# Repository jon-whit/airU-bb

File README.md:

airU-bb
=====
The airU project is an interdisciplinary project by University of Utah Computer Science, Chemical Engineering, and Computer Engineering students who have designed a low cost air-quality sensor platform that is suited to improving our understanding of the Wasatch Front’s air quality challenges.  The project hopes to provide:

- A broad collection of air quality data, with tools that enable individuals to visualize, interpret, and download real-time data interactively.
- Low cost air quality stations that can communicate wireless with centralized databases (be it government or commercial)
- Innovative transportation routes based on air quality index rating (long term)

Contribute
----------
Please see the contribution guidelines in [CONTRIBUTING.md](./CONTRIBUTING.md).

- Issue Tracker: https://github.com/jon-whit/airU-bb/issues
- Source Code: https://github.com/jon-whit/airU-bb

Support
-------
If you are having issues, please feel free to email us.

We have a mailing list located at: airu-help@utah.edu

License
-------
See [LICENSE.md](./LICENSE.md)

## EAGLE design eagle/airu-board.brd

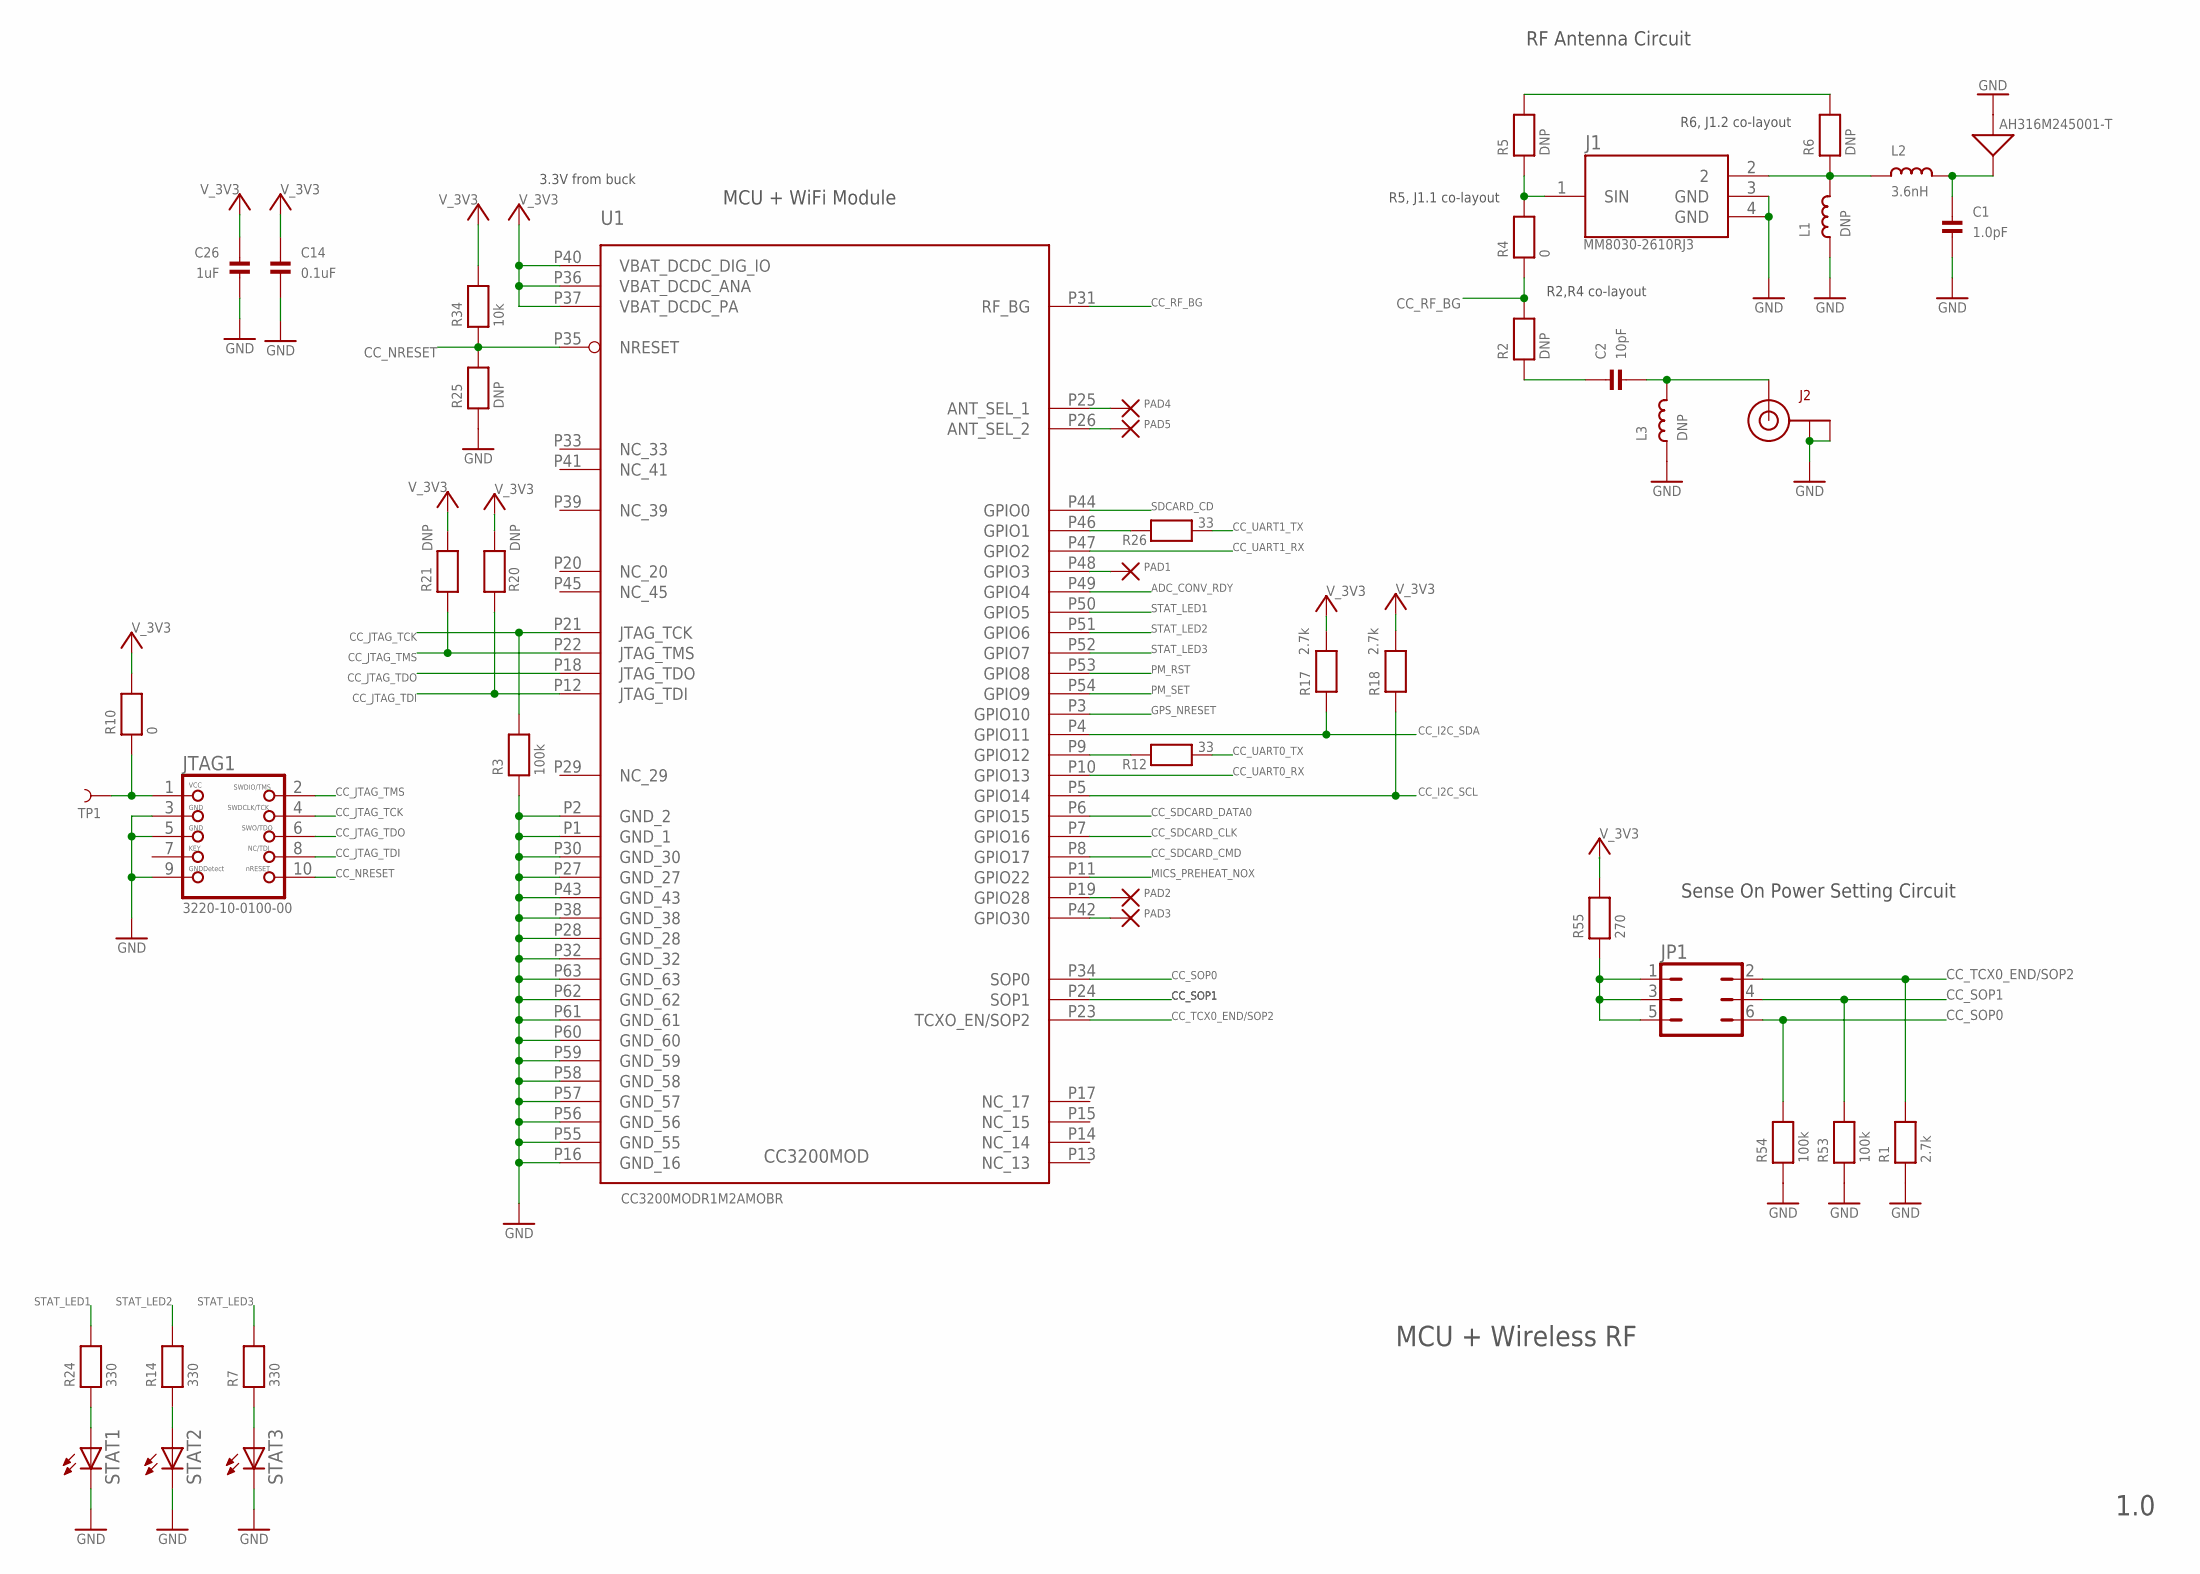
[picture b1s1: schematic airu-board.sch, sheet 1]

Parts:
C1: 1.0pF; 0402
C2: 10pF; 0402
C14: 0.1uF; 0402
C26: 1uF; 0402
E1: AH316M245001-T; AH316M
J1: MM8030-2610RJ3; MURATA_MM8030-2610RJ3
J2: U.FL-R-SMT-1(10); U.FL
JP1: JP3Q
JTAG1: 3220-10-0100-00; CORTEXM3_SWD10_MOLEX; MANUFACTURER_PART_NUMBER 3220-10-0100-00
L1, L3: DNP; _0402
L2: 3.6nH; _0402
PAD1, PAD2, PAD3, PAD4, PAD5: 2,54/1,0
R1, R17, R18: 2.7k; 0402
R2, R5, R6, R20, R21, R25: DNP; 0402
R3, R53, R54: 100k; 0402
R4, R10: 0; 0402
R7, R14, R24: 330; 0402
R12, R26: 33; 0402
R34: 10k; 0402
R55: 270; 0402
STAT1, STAT2, STAT3: LEDCHIPLED_0603; CHIPLED_0603
TP1: TEST-POINT2; PAD.02X.02
U1: CC3200MODR1M2AMOBR; CC3200MOD

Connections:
ADC_CONV_RDY: U1.P49 (GPIO4); also elsewhere on the board
CC_I2C_SCL: R18.1, U1.P5 (GPIO14); also elsewhere on the board
CC_I2C_SDA: R17.1, U1.P4 (GPIO11); also elsewhere on the board
CC_JTAG_TCK: JTAG1.4, R3.2, U1.P21 (JTAG_TCK)
CC_JTAG_TDI: JTAG1.8, R20.1, U1.P12 (JTAG_TDI)
CC_JTAG_TDO: JTAG1.6, U1.P18 (JTAG_TDO)
CC_JTAG_TMS: JTAG1.2, R21.1, U1.P22 (JTAG_TMS)
CC_NRESET: JTAG1.10, R25.2, R34.1, U1.P35 (NRESET); also elsewhere on the board
CC_RF_BG: R2.2, R4.1, U1.P31 (RF_BG)
CC_SDCARD_CLK: U1.P7 (GPIO16); also elsewhere on the board
CC_SDCARD_CMD: U1.P8 (GPIO17); also elsewhere on the board
CC_SDCARD_DATA0: U1.P6 (GPIO15); also elsewhere on the board
CC_SOP0: JP1.6, R54.2, U1.P34 (SOP0)
CC_SOP1: JP1.4, R53.2, U1.P24 (SOP1)
CC_TCX0_END/SOP2: JP1.2, R1.2, U1.P23 (TCXO_EN/SOP2)
CC_UART0_RX: U1.P10 (GPIO13); also elsewhere on the board
CC_UART0_TX: R12.2; also elsewhere on the board
CC_UART1_RX: U1.P47 (GPIO2); also elsewhere on the board
CC_UART1_TX: R26.2; also elsewhere on the board
GND: C1.2, C14.2, C26.2, E1.P$2, J1.3 (GND), J1.4 (GND), J2.1 (GND), J2.2 (GND), JTAG1.3, JTAG1.5, JTAG1.9, L1.1, L3.1, R1.1, R3.1, R25.1, R53.1, R54.1, STAT1.C, STAT2.C, STAT3.C, U1.P1 (GND_1), U1.P2 (GND_2), U1.P16 (GND_16), U1.P27 (GND_27), U1.P28 (GND_28), U1.P30 (GND_30), U1.P32 (GND_32), U1.P38 (GND_38), U1.P43 (GND_43), U1.P55 (GND_55), U1.P56 (GND_56), U1.P57 (GND_57), U1.P58 (GND_58), U1.P59 (GND_59), U1.P60 (GND_60), U1.P61 (GND_61), U1.P62 (GND_62), U1.P63 (GND_63); also elsewhere on the board
GPS_NRESET: U1.P3 (GPIO10); also elsewhere on the board
MICS_PREHEAT_NOX: U1.P11 (GPIO22); also elsewhere on the board
unnamed: J1.1 (SIN), R4.2, R5.1
unnamed: R5.2, R6.2
unnamed: J1.2, L1.2, L2.1, R6.1
unnamed: C1.1, E1.P$1, L2.2
unnamed: C2.1, R2.1
unnamed: C2.2, J2.3 (SIGNAL), L3.2
unnamed: JTAG1.1, R10.1, TP1.P$1
unnamed: R12.1, U1.P9 (GPIO12)
unnamed: R26.1, U1.P46 (GPIO1)
unnamed: R24.1, STAT1.A
unnamed: R14.1, STAT2.A
unnamed: R7.1, STAT3.A
unnamed: PAD1.1, U1.P48 (GPIO3)
unnamed: PAD2.1, U1.P19 (GPIO28)
unnamed: PAD3.1, U1.P42 (GPIO30)
unnamed: PAD4.1, U1.P25 (ANT_SEL_1)
unnamed: PAD5.1, U1.P26 (ANT_SEL_2)
unnamed: JP1.1, JP1.3, JP1.5, R55.1
PM_RST: U1.P53 (GPIO8); also elsewhere on the board
PM_SET: U1.P54 (GPIO9); also elsewhere on the board
SDCARD_CD: U1.P44 (GPIO0); also elsewhere on the board
STAT_LED1: R24.2, U1.P50 (GPIO5)
STAT_LED2: R14.2, U1.P51 (GPIO6)
STAT_LED3: R7.2, U1.P52 (GPIO7)
V_3V3: C14.1, C26.1, R10.2, R17.2, R18.2, R20.2, R21.2, R34.2, R55.2, U1.P36 (VBAT_DCDC_ANA), U1.P37 (VBAT_DCDC_PA), U1.P40 (VBAT_DCDC_DIG_IO); also elsewhere on the board

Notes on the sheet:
R2,R4 co-layout
R5, J1.1 co-layout
R6, J1.2 co-layout
3.3V from buck
1.0
MCU + Wireless RF
RF Antenna Circuit
Sense On Power Setting Circuit
MCU + WiFi Module

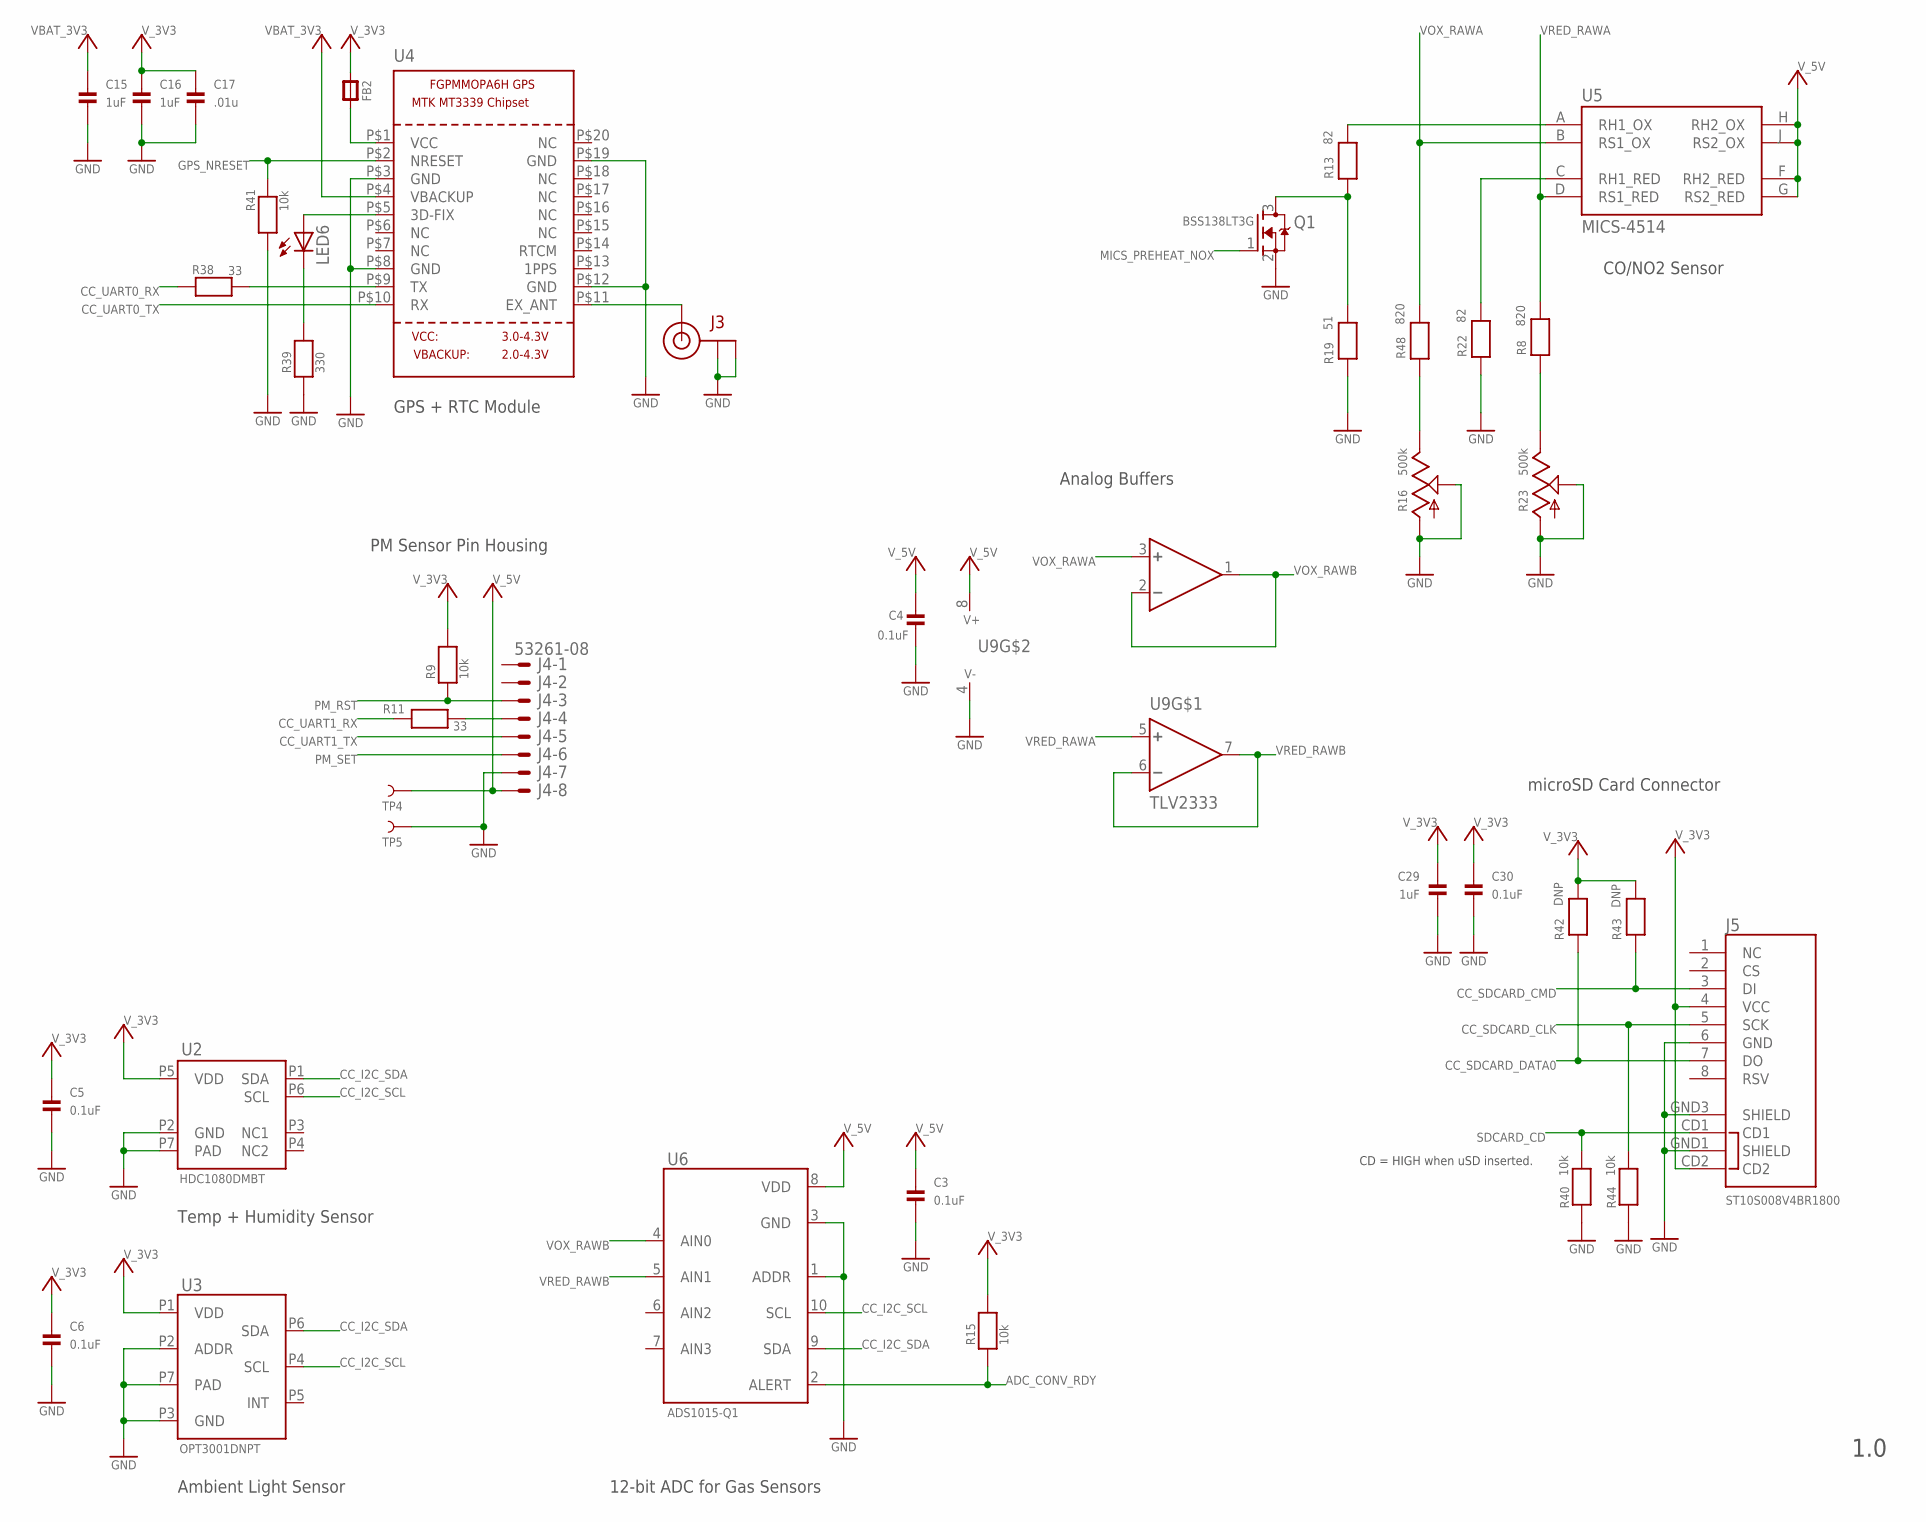
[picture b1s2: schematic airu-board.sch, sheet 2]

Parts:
C3, C4, C5, C6, C30: 0.1uF; _0402
C15, C16, C29: 1uF; _0402
C17: .01u; _0402
FB2: FERRITE_0402; _0402
J3: U.FL-R-SMT-1(10); U.FL
J4: 53261-08
J5: ST10S008V4BR1800; MICROSD_1:1; MANUFACTURER_PART_NUMBER ST10S008V4BR1800
LED6: LEDCHIPLED_0603; CHIPLED_0603
Q1: BSS138LT3G; SOT23
R8, R48: 820; 0402
R9, R15, R40, R41, R44: 10k; 0402
R11, R38: 33; 0402
R13, R22: 82; 0402
R16, R23: 500k; B25P
R19: 51; 0402
R39: 330; 0402
R42, R43: DNP; 0402
TP4, TP5: TEST-POINT2; PAD.02X.02
U2: HDC1080DMBT; WSON
U3: OPT3001DNPT; USON
U4: GPS_FGPMMOPA6H; FGPMMOPA6H
U5: MICS-4514; MICS_10-SMD
U6: ADS1015-Q1; S-PDSO-G10
U9: TLV2333; DGK_S-PDSO-G8

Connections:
ADC_CONV_RDY: R15.1, U6.2 (ALERT); also elsewhere on the board
CC_I2C_SCL: U2.P6 (SCL), U3.P4 (SCL), U6.10 (SCL); also elsewhere on the board
CC_I2C_SDA: U2.P1 (SDA), U3.P6 (SDA), U6.9 (SDA); also elsewhere on the board
CC_SDCARD_CLK: J5.5 (SCK), R44.2; also elsewhere on the board
CC_SDCARD_CMD: J5.3 (DI), R43.1; also elsewhere on the board
CC_SDCARD_DATA0: J5.7 (DO), R42.1; also elsewhere on the board
CC_UART0_RX: R38.1; also elsewhere on the board
CC_UART0_TX: U4.P$10 (RX); also elsewhere on the board
CC_UART1_RX: R11.1; also elsewhere on the board
CC_UART1_TX: J4.5; also elsewhere on the board
GND: C3.2, C4.2, C5.2, C6.2, C15.2, C16.2, C17.2, C29.2, C30.2, J3.1 (GND), J3.2 (GND), J4.7, J5.6 (GND), J5.GND1 (SHIELD), J5.GND3 (SHIELD), Q1.2 (S), R16.A, R16.S, R19.1, R22.1, R23.A, R23.S, R39.1, R40.1, R41.1, R44.1, TP5.P$1, U2.P2 (GND), U2.P7 (PAD), U3.P2 (ADDR), U3.P3 (GND), U3.P7 (PAD), U4.P$3 (GND), U4.P$8 (GND), U4.P$12 (GND), U4.P$19 (GND), U6.1 (ADDR), U6.3 (GND), U9.4 (V-); also elsewhere on the board
GPS_NRESET: R41.2, U4.P$2 (NRESET); also elsewhere on the board
MICS_PREHEAT_NOX: Q1.1 (G); also elsewhere on the board
unnamed: J4.4, R11.2
unnamed: R13.2, U5.A (RH1_OX)
unnamed: Q1.3 (D), R13.1, R19.2
unnamed: R22.2, U5.C (RH1_RED)
unnamed: R16.E, R48.1
unnamed: R8.1, R23.E
unnamed: J3.3 (SIGNAL), U4.P$11 (EX_ANT)
unnamed: LED6.A, U4.P$5 (3D-FIX)
unnamed: LED6.C, R39.2
unnamed: R38.2, U4.P$9 (TX)
PM_RST: J4.3, R9.1; also elsewhere on the board
PM_SET: J4.6; also elsewhere on the board
SDCARD_CD: J5.CD1, R40.2; also elsewhere on the board
VBAT_3V3: C15.1, U4.P$4 (VBACKUP); also elsewhere on the board
VOX_RAWA: R48.2, U5.B (RS1_OX), U9.3 (+)
VOX_RAWB: U6.4 (AIN0), U9.1 (OUT), U9.2 (-)
VRED_RAWA: R8.2, U5.D (RS1_RED), U9.5 (+1)
VRED_RAWB: U6.5 (AIN1), U9.6 (-1), U9.7 (OUT1)
V_3V3: C5.1, C6.1, C16.1, C17.1, C29.1, C30.1, FB2.1, FB2.2, J5.4 (VCC), J5.CD2, R9.2, R15.2, R42.2, R43.2, U2.P5 (VDD), U3.P1 (VDD), U4.P$1 (VCC); also elsewhere on the board
V_5V: C3.1, C4.1, J4.8, TP4.P$1, U5.F (RH2_RED), U5.G (RS2_RED), U5.H (RH2_OX), U5.J (RS2_OX), U6.8 (VDD), U9.8 (V+); also elsewhere on the board

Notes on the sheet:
CD = HIGH when uSD inserted.
1.0
GPS + RTC Module
Temp + Humidity Sensor
Ambient Light Sensor
PM Sensor Pin Housing
microSD Card Connector
CO/NO2 Sensor
12-bit ADC for Gas Sensors
Analog Buffers

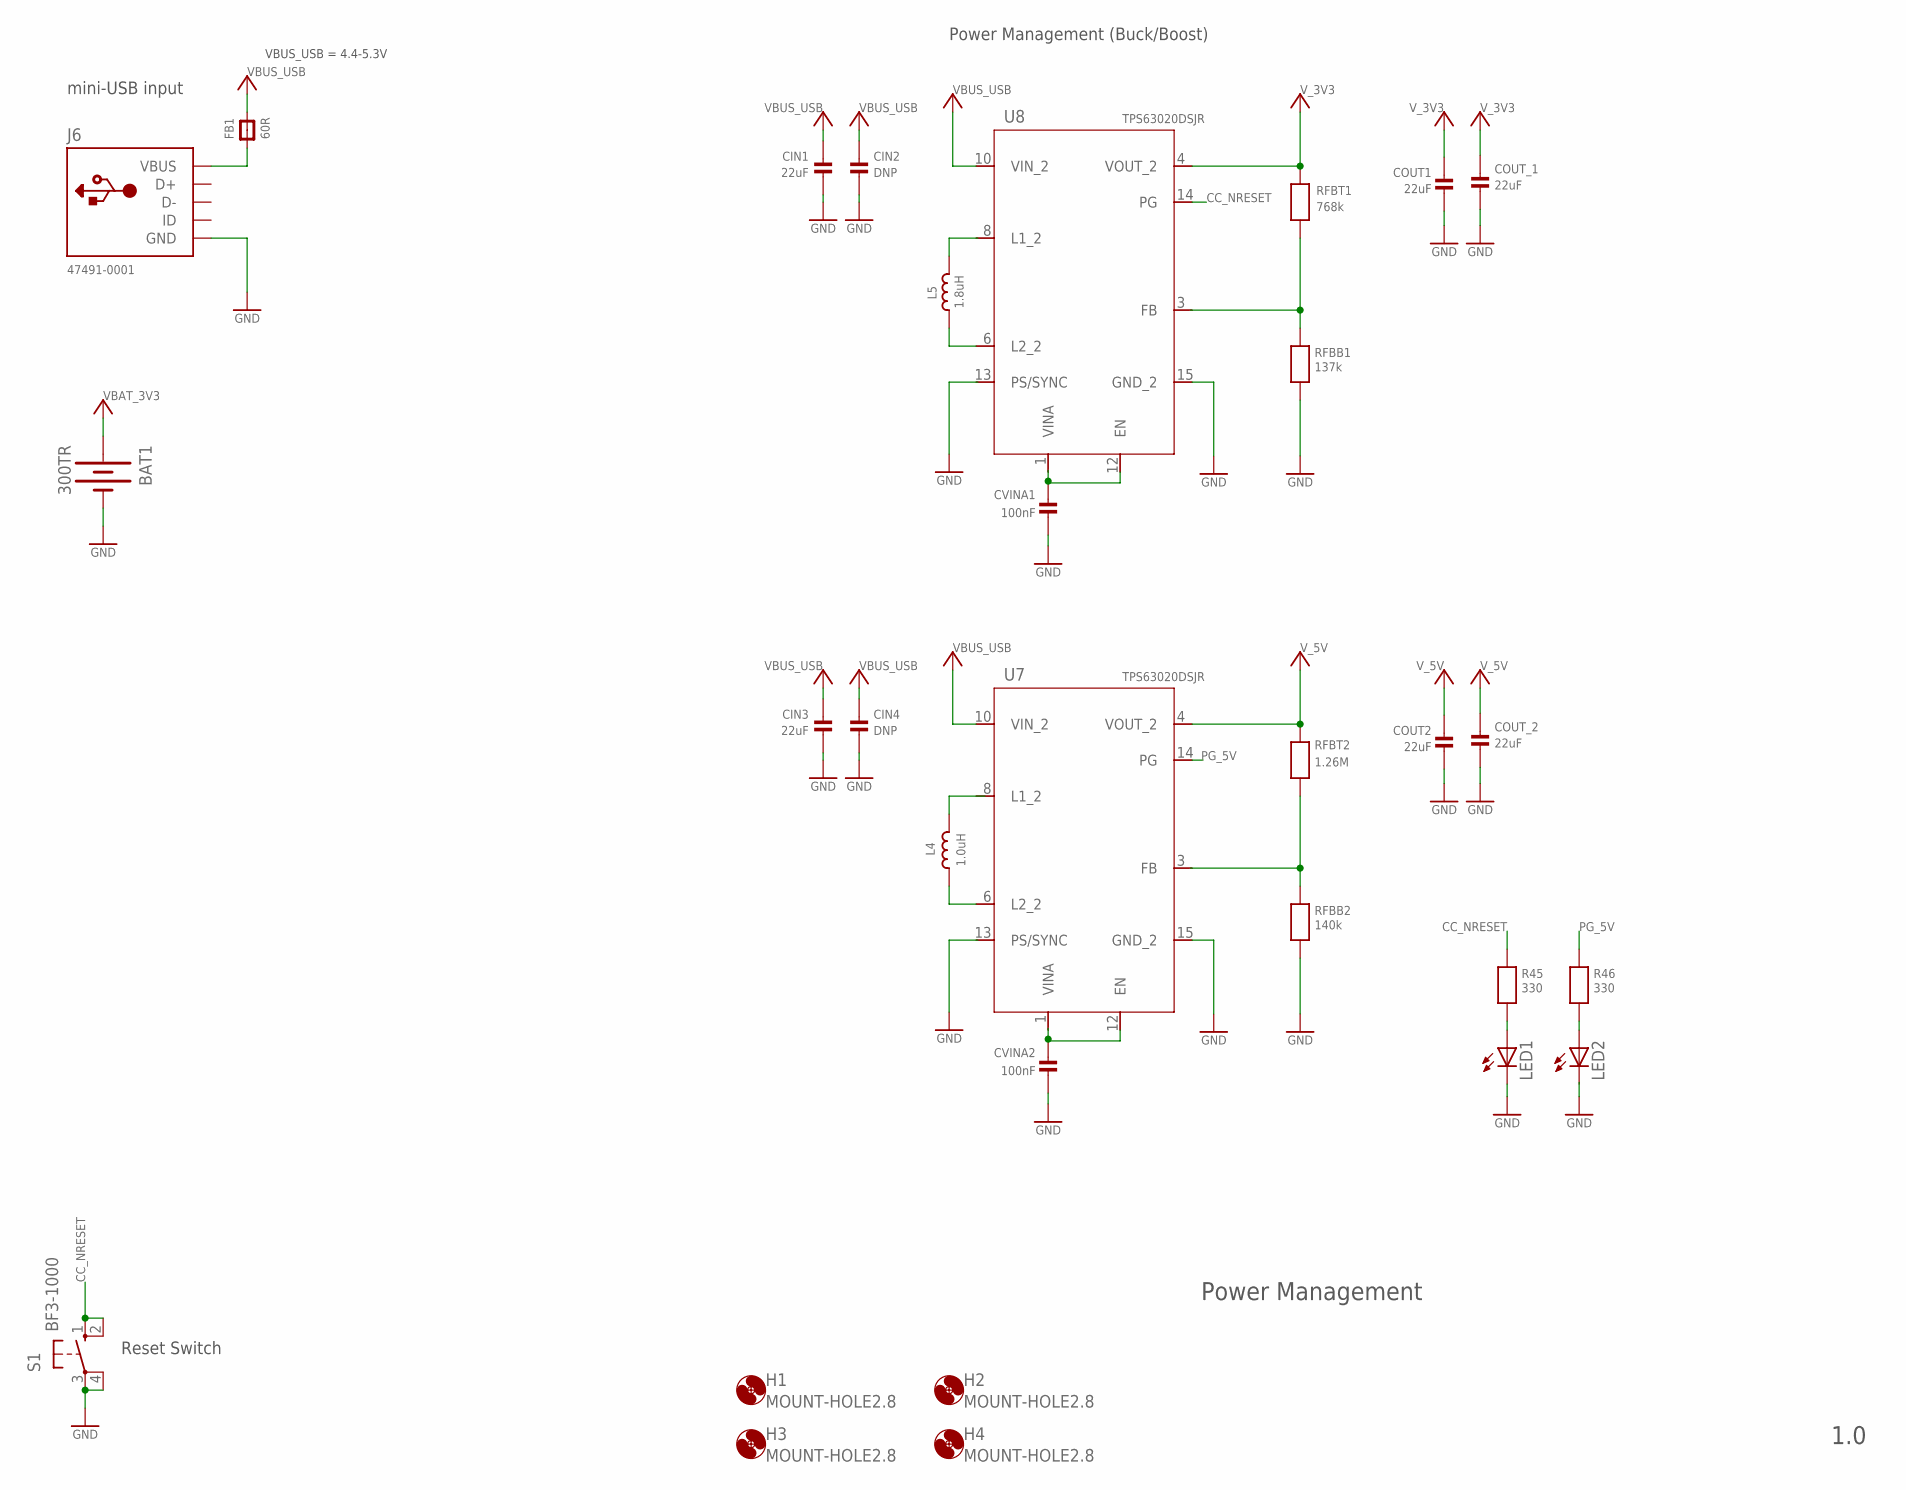
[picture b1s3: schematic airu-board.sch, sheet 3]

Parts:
BAT1: 300TR; BATTCON_12MM; MANUFACTURER_PART_NUMBER 300TR
CIN1, CIN3: 22uF; 1206_190
CIN2, CIN4: DNP; 1206_190
COUT1, COUT2: 22uF; 0805
COUT_1, COUT_2: 22uF; 0805
CVINA1, CVINA2: 100nF; 0603
FB1: 60R; _0402
H1, H2, H3, H4: MOUNT-HOLE2.8; 2,8
J6: 47491-0001; USB-MINIB; MANUFACTURER_PART_NUMBER 47491-0001
L4: 1.0uH; SRN3015
L5: 1.8uH; SDR0403
LED1, LED2: LEDCHIPLED_0603; CHIPLED_0603
R45, R46: 330; 0402
RFBB1: 137k; 0402
RFBB2: 140k; 0402
RFBT1: 768k; 0402
RFBT2: 1.26M; 0805
S1: BF3-1000; B3F-10XX
U7, U8: TPS63020DSJR; R-PVSON-N14

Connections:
CC_NRESET: R45.P1 (1), S1.1 (S), S1.2 (S1), U8.14 (PG); also elsewhere on the board
GND: BAT1.GND (-), CIN1.2, CIN2.2, CIN3.2, CIN4.2, COUT1.2, COUT2.2, COUT_1.2, COUT_2.2, CVINA1.2, CVINA2.2, J6.GND, LED1.C, RFBB1.P2 (2), RFBB2.P2 (2), S1.3, S1.4 (P1), U7.15 (GND_2), U8.15 (GND_2); also elsewhere on the board
unnamed: CVINA1.1, U8.12 (EN)
unnamed: L5.1, U8.6 (L2_2)
unnamed: L4.1, U7.6 (L2_2)
unnamed: RFBB1.P1 (1), RFBT1.P2 (2)
unnamed: RFBB2.P1 (1), RFBT2.2
unnamed: CVINA2.1, U7.12 (EN)
unnamed: LED2.A, R46.P2 (2)
unnamed: LED1.A, R45.P2 (2)
unnamed: FB1.1, J6.VBUS
PG_5V: R46.P1 (1), U7.14 (PG)
VBAT_3V3: BAT1.PWR@1 (+); also elsewhere on the board
VBUS_USB: CIN1.1, CIN2.1, CIN3.1, CIN4.1, FB1.2, U7.10 (VIN_2), U8.10 (VIN_2)
V_3V3: COUT1.1, COUT_1.1, RFBT1.P1 (1), U8.4 (VOUT_2); also elsewhere on the board
V_5V: COUT2.1, COUT_2.1, RFBT2.1, U7.4 (VOUT_2); also elsewhere on the board

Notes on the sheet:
Reset Switch
VBUS_USB = 4.4-5.3V
Power Management
1.0
Power Management (Buck/Boost)
mini-USB input

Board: 2 copper layers, 113 parts (12 on the bottom side), 74 nets, no tracks yet.

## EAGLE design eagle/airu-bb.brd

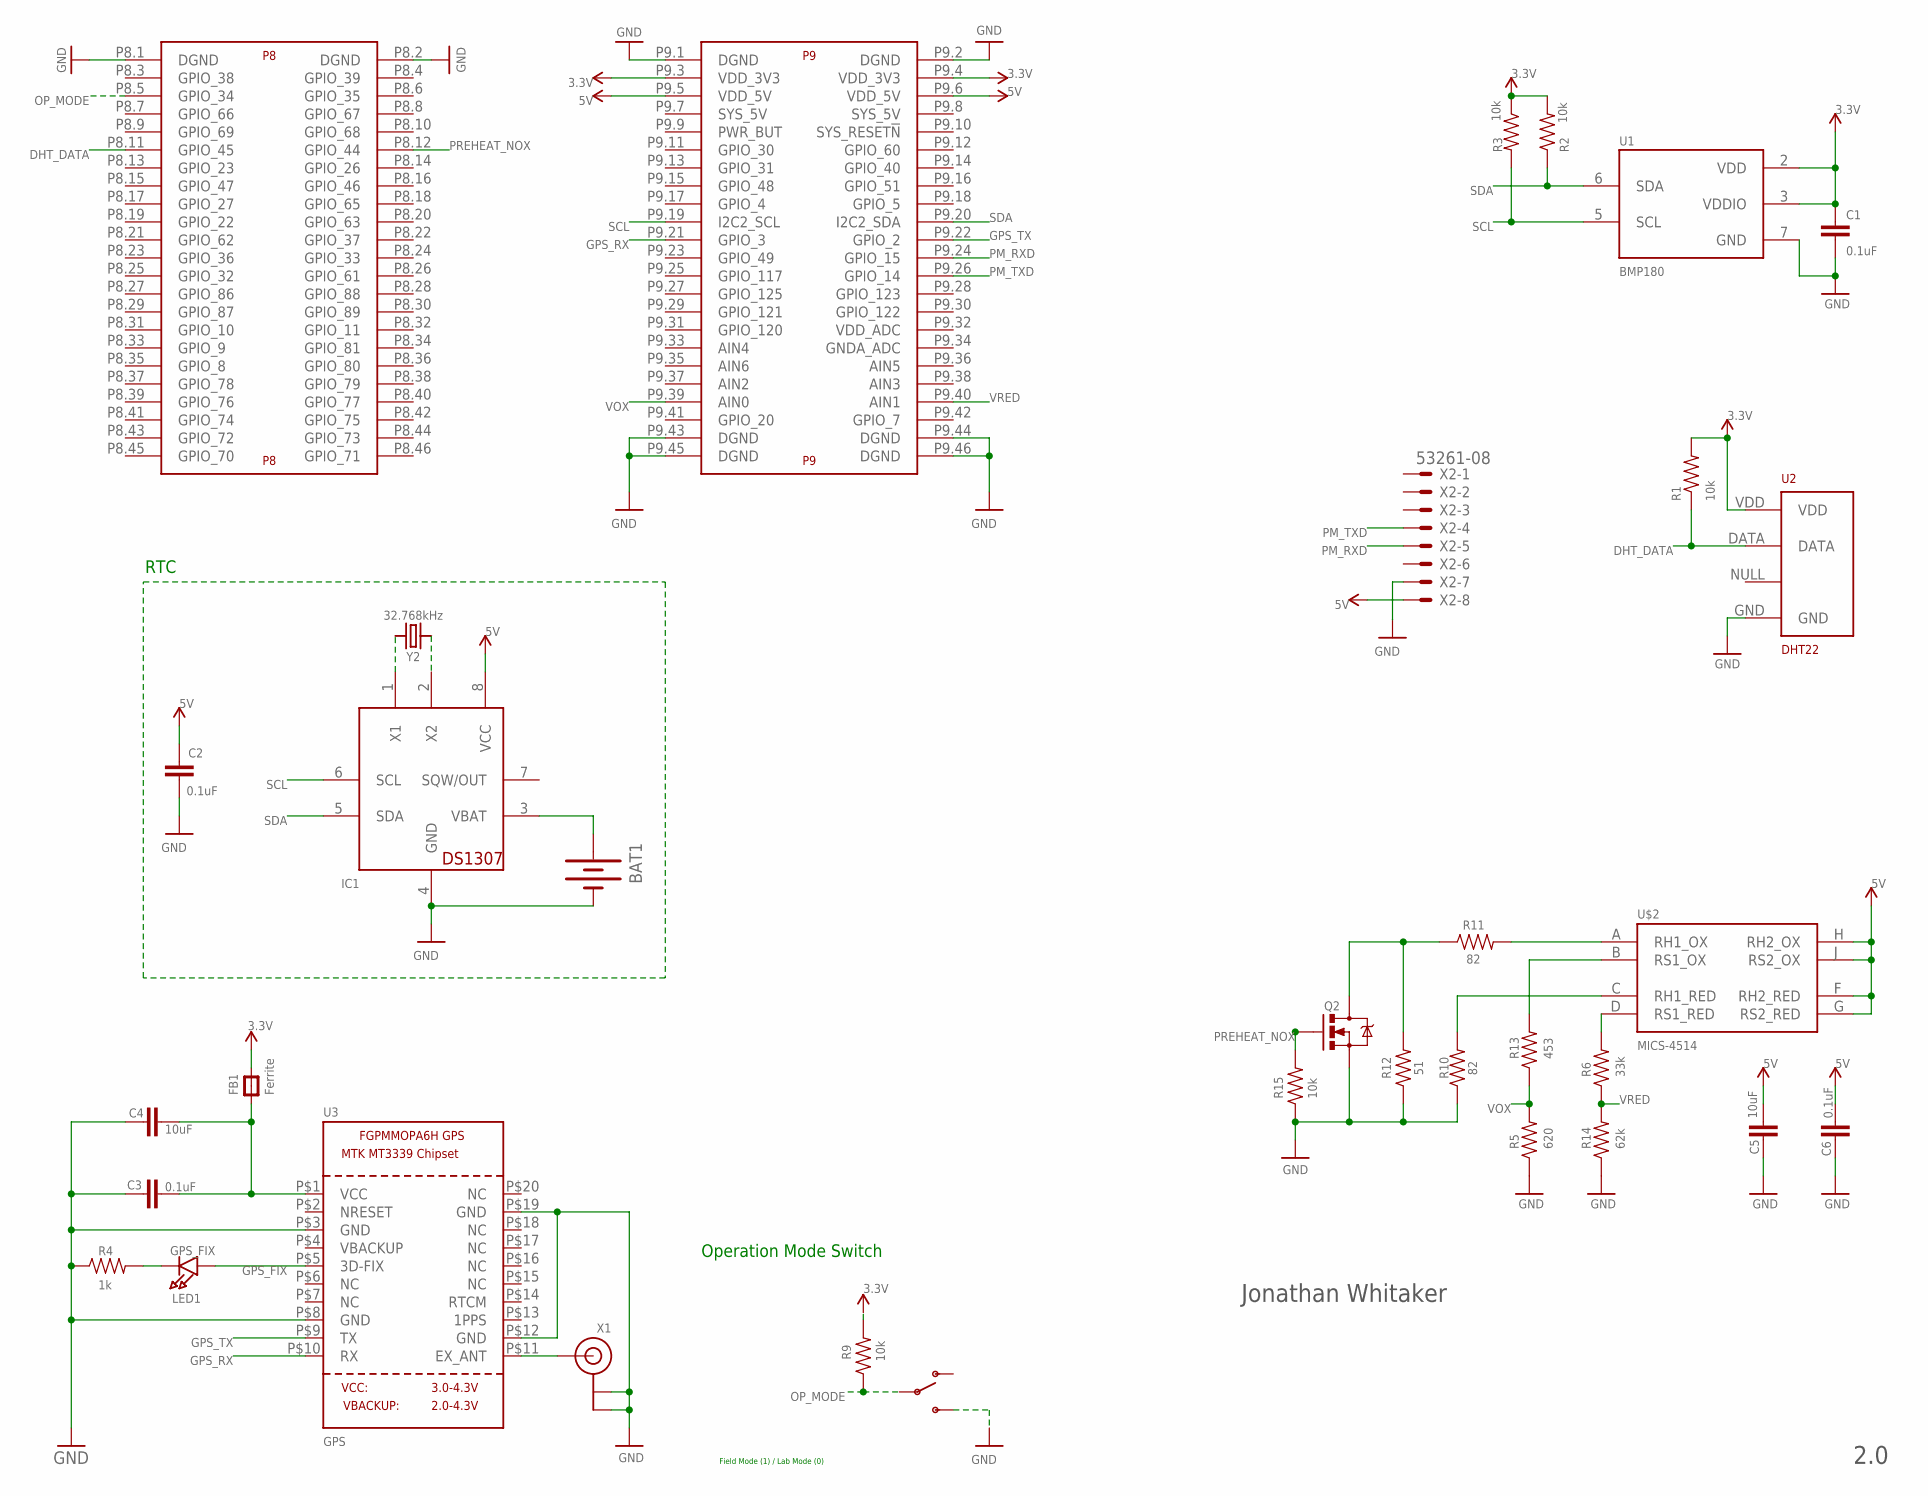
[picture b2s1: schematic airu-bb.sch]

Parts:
BAT1: BATTERY20SMD; BATTCON_20MM
C1, C2, C3, C6: 0.1uF; 1206
C4, C5: 10uF; 1206
FB1: Ferrite; 0805
IC1: DS1307; DIL08
LED1: GPS_FIX; CHIPLED_1206
Q2: MOSFET-NCHANNELAO3404A; SOT23-3
R1, R2, R3, R9, R15: 10k; 1206
R4: 1k; 1206
R5: 620; 1206
R6: 33k; 1206
R10, R11: 82; 1206
R12: 51; 1206
R13: 453; 1206
R14: 62k; 1206
U1: BMP180
U2: DHT22; RHT03_DHT-22
U3: GPS; FGPMMOPA6H
U$1: BEAGLE_BONE_BLACK_CAPE
U$2: MICS-4514; MICS_10-SMD
U$3: SWITCH_SPDT; KPS-1290
X1: ANTENNA_U.FL; U.FL
X2: 53261-08
Y2: 32.768kHz; 2-SMD

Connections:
3.3V: C1.1, FB1.2, R1.2, R2.2, R3.1, R9.2, U1.2 (VDD), U1.3 (VDDIO), U2.VDD, U$1.P9.3 (VDD_3V3), U$1.P9.4 (VDD_3V3)
5V: C2.2, C5.2, C6.2, IC1.8 (VCC), U$1.P9.5 (VDD_5V), U$1.P9.6 (VDD_5V), U$2.F (RH2_RED), U$2.G (RS2_RED), U$2.H (RH2_OX), U$2.J (RS2_OX), X2.8
DHT_DATA: R1.1, U2.DATA, U$1.P8.11 (GPIO_45)
GND: BAT1.2 (-), C1.2, C2.1, C3.1, C4.1, C5.1, C6.1, IC1.4 (GND), Q2.2 (S), R4.1, R5.1, R10.1, R12.1, R14.1, R15.1, U1.7 (GND), U2.GND, U3.P$3 (GND), U3.P$8 (GND), U3.P$12 (GND), U3.P$19 (GND), U$1.P8.1 (DGND), U$1.P8.2 (DGND), U$1.P9.1 (DGND), U$1.P9.2 (DGND), U$1.P9.43 (DGND), U$1.P9.44 (DGND), U$1.P9.45 (DGND), U$1.P9.46 (DGND), U$3.S, X1.1 (GND), X1.2 (GND), X2.7
GPS_FIX: LED1.A, U3.P$5 (3D-FIX)
GPS_RX: U3.P$10 (RX), U$1.P9.21 (GPIO_3)
GPS_TX: U3.P$9 (TX), U$1.P9.22 (GPIO_2)
unnamed: C3.2, C4.2, FB1.1, U3.P$1 (VCC)
unnamed: U3.P$11 (EX_ANT), X1.3 (SIGNAL)
unnamed: LED1.C, R4.2
unnamed: R10.2, U$2.C (RH1_RED)
unnamed: R13.2, U$2.B (RS1_OX)
unnamed: Q2.3 (D), R11.1, R12.2
unnamed: R6.2, U$2.D (RS1_RED)
unnamed: R11.2, U$2.A (RH1_OX)
unnamed: BAT1.1 (+), IC1.3 (VBAT)
unnamed: IC1.1 (X1), Y2.1
unnamed: IC1.2 (X2), Y2.2
OP_MODE: R9.1, U$1.P8.5 (GPIO_34), U$3.P
PM_RXD: U$1.P9.24 (GPIO_15), X2.5
PM_TXD: U$1.P9.26 (GPIO_14), X2.4
PREHEAT_NOX: Q2.1 (G), R15.2, U$1.P8.12 (GPIO_44)
SCL: IC1.6 (SCL), R3.2, U1.5 (SCL), U$1.P9.19 (I2C2_SCL)
SDA: IC1.5 (SDA), R2.1, U1.6 (SDA), U$1.P9.20 (I2C2_SDA)
VOX: R5.2, R13.1, U$1.P9.39 (AIN0)
VRED: R6.1, R14.2, U$1.P9.40 (AIN1)

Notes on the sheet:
Jonathan Whitaker
2.0
RTC
Operation Mode Switch
Field Mode (1) / Lab Mode (0)

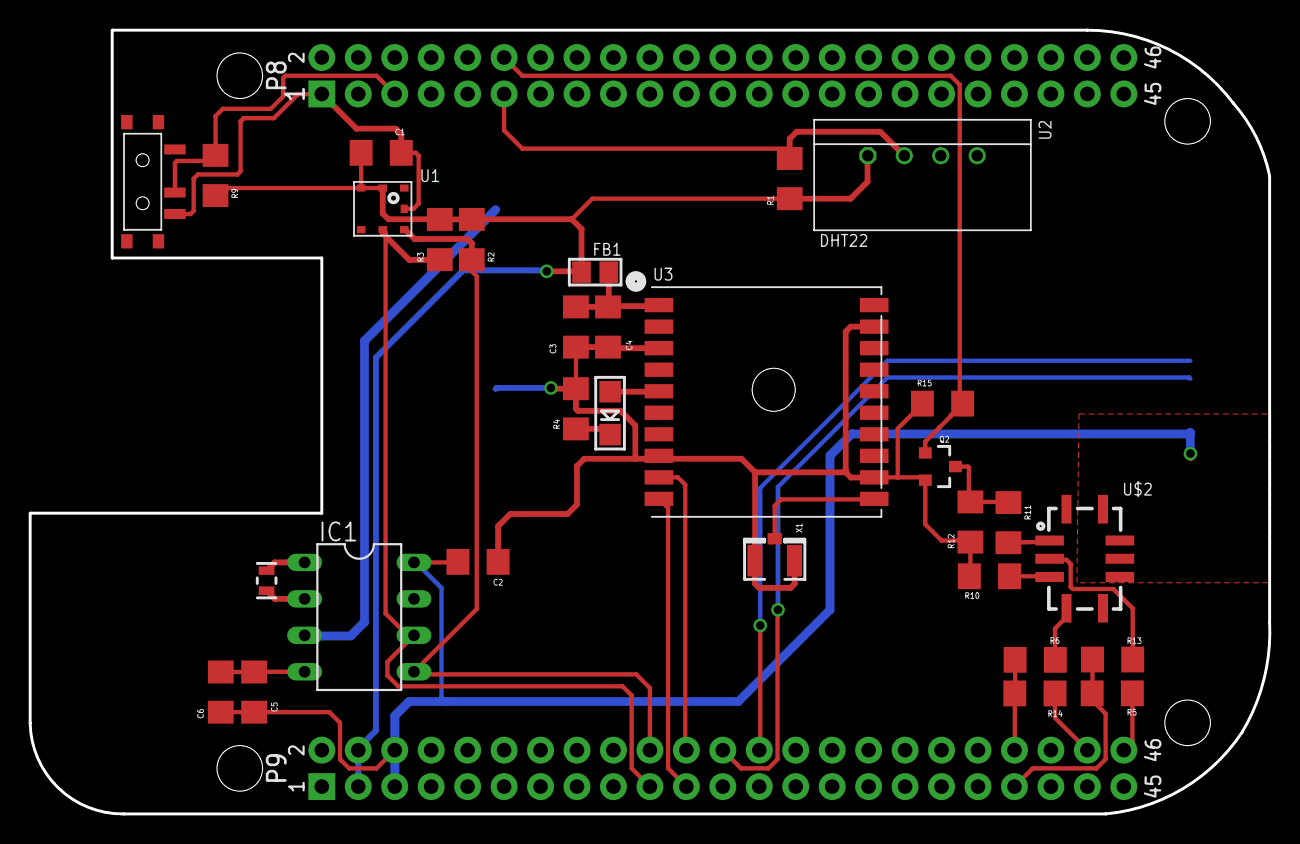
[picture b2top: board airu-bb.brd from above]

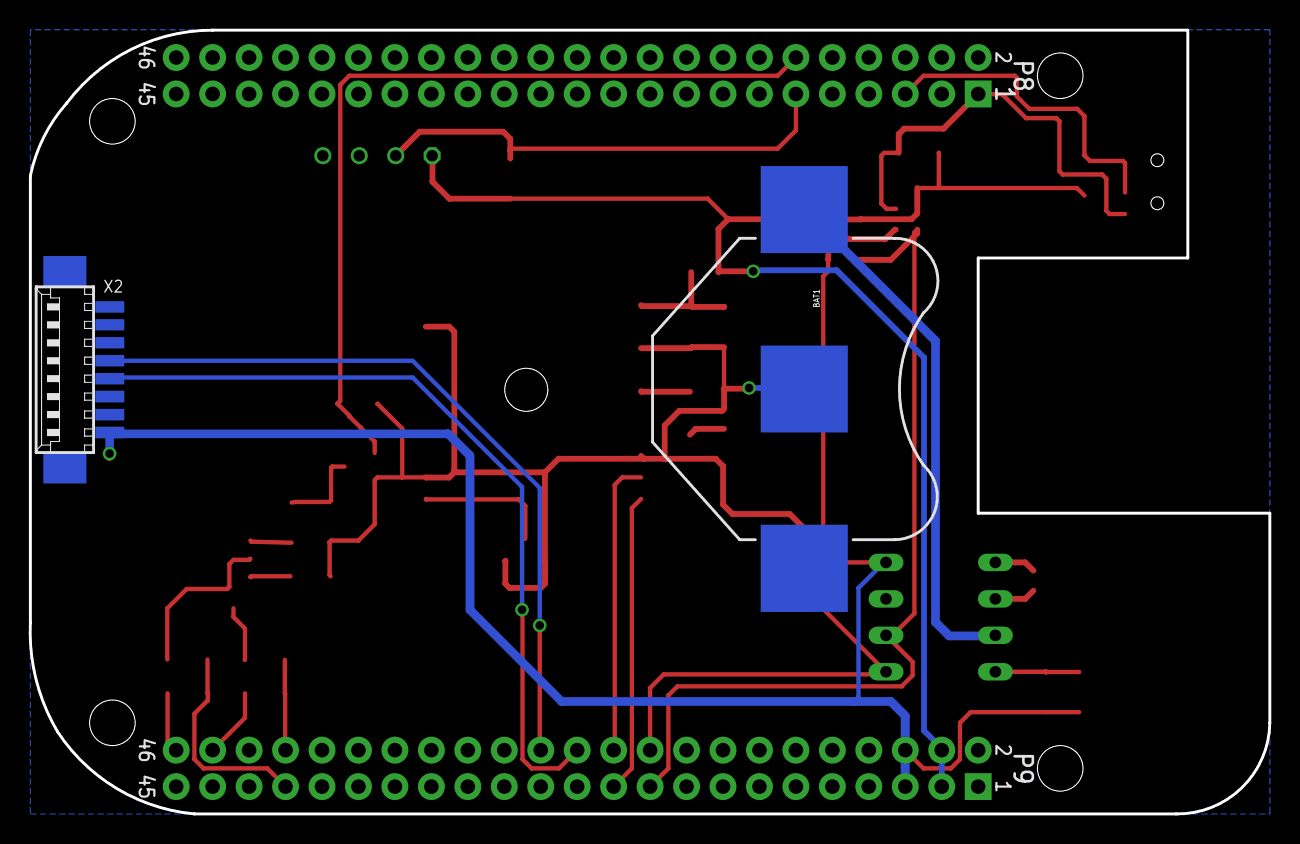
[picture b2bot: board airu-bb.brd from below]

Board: 2 copper layers, 86.4 x 54.6 mm, 33 parts (2 on the bottom side), 26 nets.

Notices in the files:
parts and their libraries:
SparkFun-Passives: Licensing: Creative Commons ShareAlike 4.0 International - https://creativecommons.org/licenses/by-sa/4.0
microbuilder: This work is placed in the public domain, and may be freely used for commercial and non-commercial work with the following conditions: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
